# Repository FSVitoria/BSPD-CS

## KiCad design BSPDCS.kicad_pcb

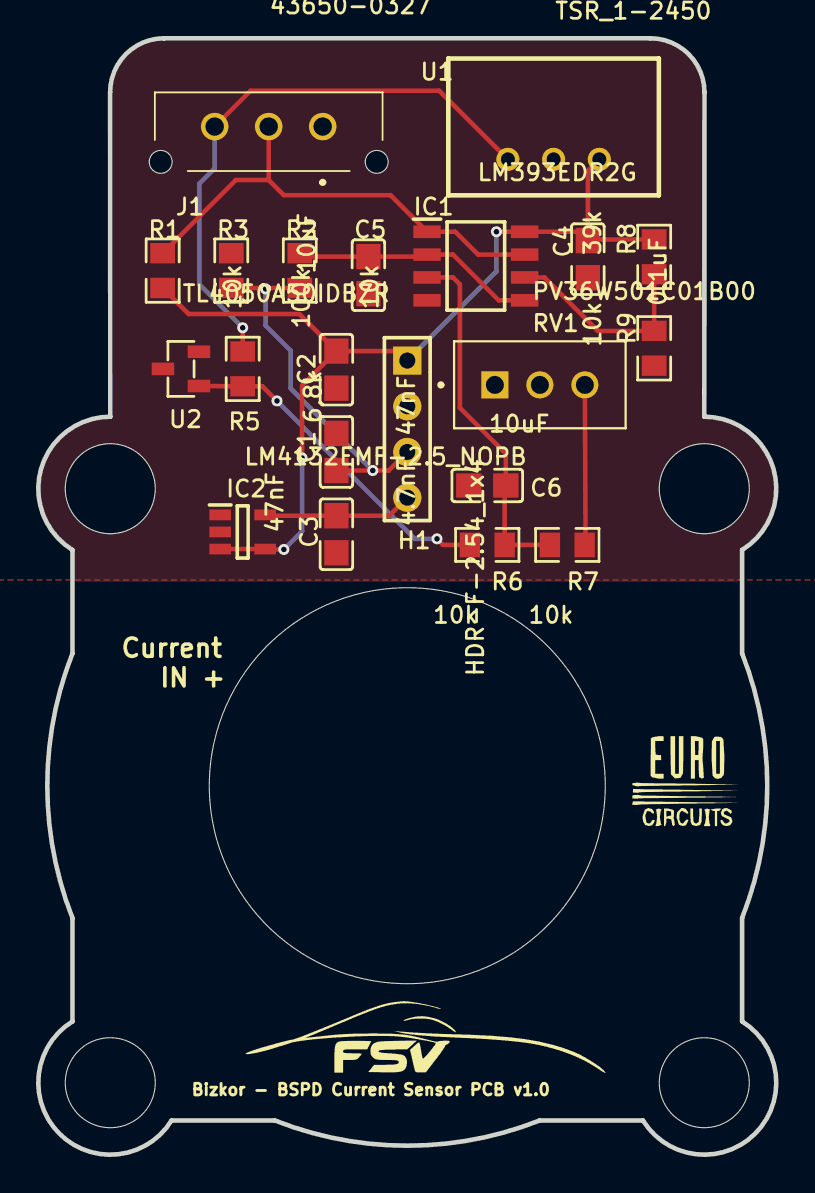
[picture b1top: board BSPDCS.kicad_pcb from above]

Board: 2 copper layers, 41.0 x 62.0 mm, 26 parts (0 on the bottom side), 11 nets.

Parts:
C1: 4.7nF; C0805
C2, C3: 47nF; C0805
C4: 0.1uF; C0805
C5, C6: 10uF; C0805
H1: HDR-F-2.54_1x4; HDR-F-2.54_1X4
Hole_gge2671: Hole_gge2671
Hole_gge2683: Hole_gge2683
Hole_gge2695: Hole_gge2695
Hole_gge2707: Hole_gge2707
Hole_gge2719: Hole_gge2719
IC1: LM393EDR2G; SOIC127P600X175-8N
IC2: LM4132EMF-2.5_NOPB; SOT95P280X145-5N
J1: 43650-0327; 436500327
R1, R2, R6, R7, R9: 10k; R0805_NEW
R3: 100k; R0805_NEW
R5: 6,8k; R0805_NEW
R8: 39k; R0805_NEW
RV1: PV36W501C01B00; TRIM_PV36W501C01B00
U1: TSR_1-2450; TSR-1-24120
U2: TL4050A50IDBZR; SOT-23-3_L2.9-W1.3-P1.90-LS2.4-BR

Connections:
+5V: C2.1, C4.1, H1.1, IC1.8, IC2.3, IC2.4, R1.2, R8.2, U1.3
+24V: J1.3, R5.1, U1.1
CS: C1.2, H1.3, R2.2, R3.2
CS_OUT: IC1.1, IC1.7, J1.2, R1.1
CS_UL: C6.2, IC1.3, R6.1, R7.2
GND: C1.1, C2.2, C3.1, C4.2, C5.1, C6.1, H1.2, IC1.4, IC2.2, J1.1, R3.1, R9.1, RV1.2, U1.2, U2.2, U2.3
LL: IC1.6, R8.1, R9.2
R2_1: C5.2, IC1.2, IC1.5, R2.1
R5_2: R5.2, R6.2, U2.1
R7_1: R7.1, RV1.3
UREF5KW: C3.2, H1.4, IC2.5
